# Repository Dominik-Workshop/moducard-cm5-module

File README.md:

# ModuCard CM5 module

## Overview

The **ModuCard CM5 Module** is a carrier board for the **Raspberry Pi Compute Module 5**.
It is designed to interface with the  [ModuCard backplane](https://github.com/KoNarRobotics/ModuCard-backplane), to create a more complex electronics system.

The module breaks out selected CM5 interfaces to front-panel connectors and it interfaces with the backplane.

### Key Features

- **Networking:** Gigabit Ethernet (RJ45)
- **Connectivity:** 2x USB 3.0 Type-A ports
- **Display:** 1x Full-size HDMI port
- **Storage:**
  - **Micro SD** card slot (for CM5 Lite variants)
  - **M.2 M-Key** slot (PCIe x1 Gen 3) for NVMe SSDs or AI accelerators.
- **System & Debug:**
  - **USB-C** port (front panel) for serial console access
  - **USB-C** port (vertical) for flashing the CM5 via `rpiboot`.
- **Backplane I/O:**
  - 2x **FD CAN** interfaces with on-board transceivers
  - 1x **USB 2.0**
- **Cooling:** 4-pin JST connector for the CM5 cooling fan.

<p align="center">
  
  <br>
  <em>Assembled ModuCard CM5 Module with Raspberry Pi Compute Module 5 and NVMe SSD.</em>
</p>

## Project Status

**Design:** ✅ → **Fabrication & Assembly:** ✅ → **Bring-up:** ✅

The project is **complete and ready for deployment**. All core features have been validated on physical hardware.

## Used Tools

- [KiCad](https://www.kicad.org/) - Schematic and PCB design

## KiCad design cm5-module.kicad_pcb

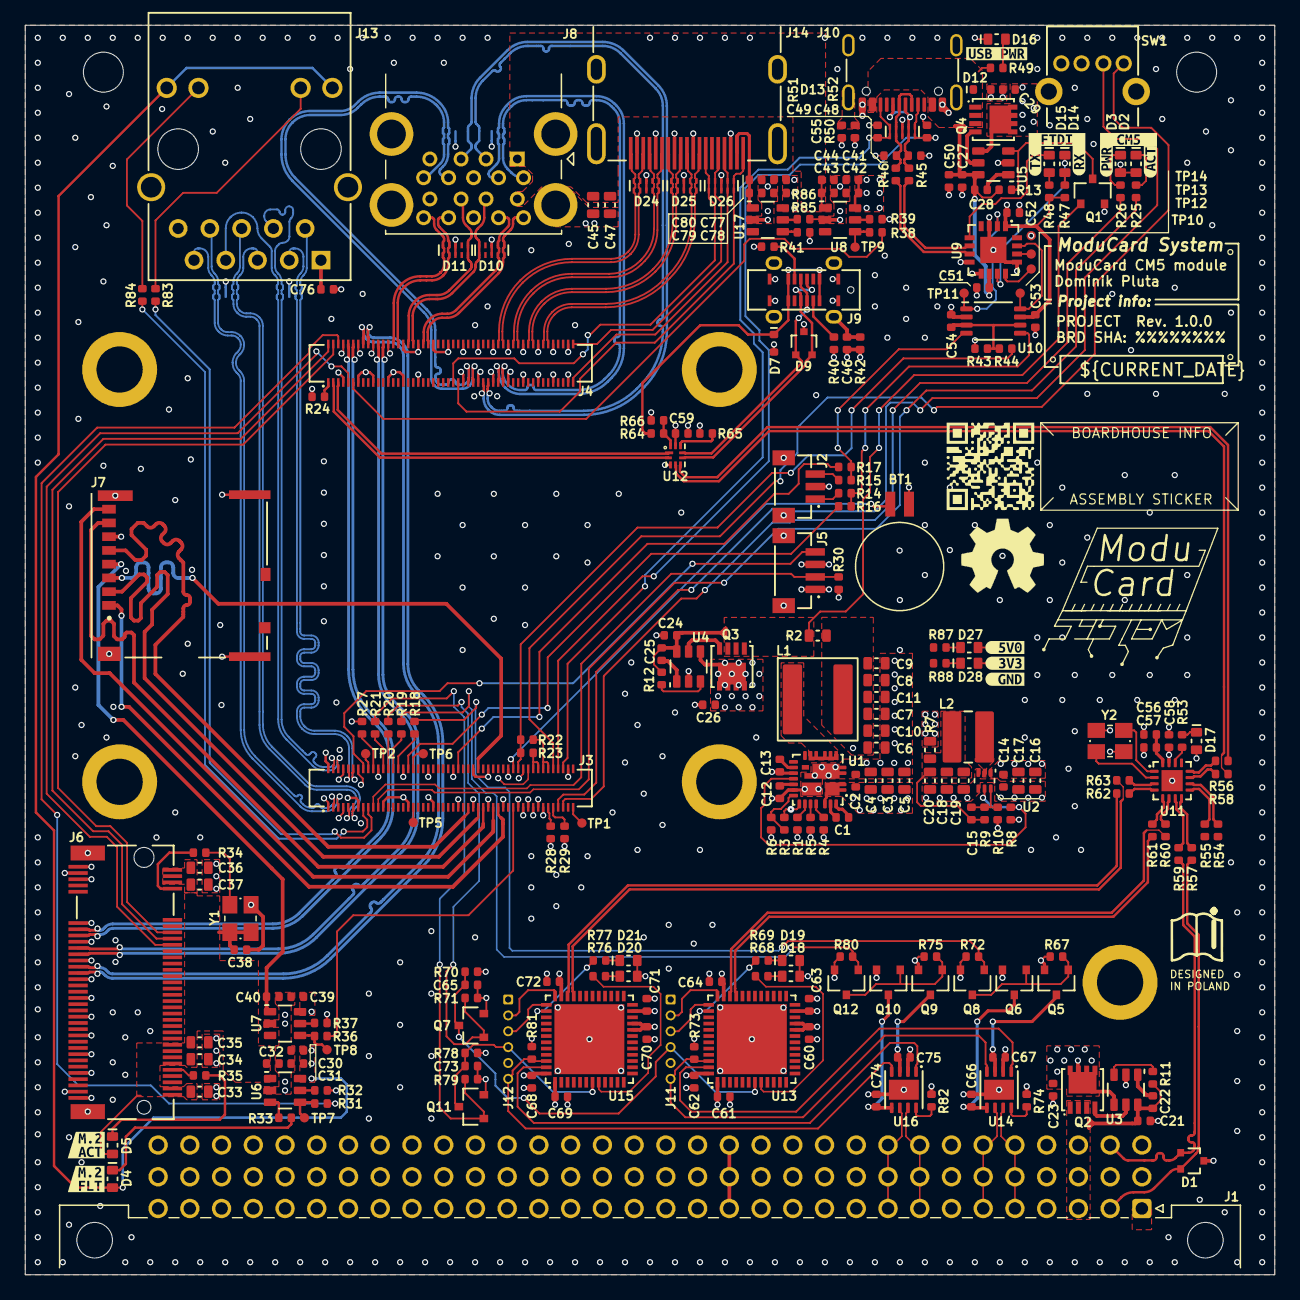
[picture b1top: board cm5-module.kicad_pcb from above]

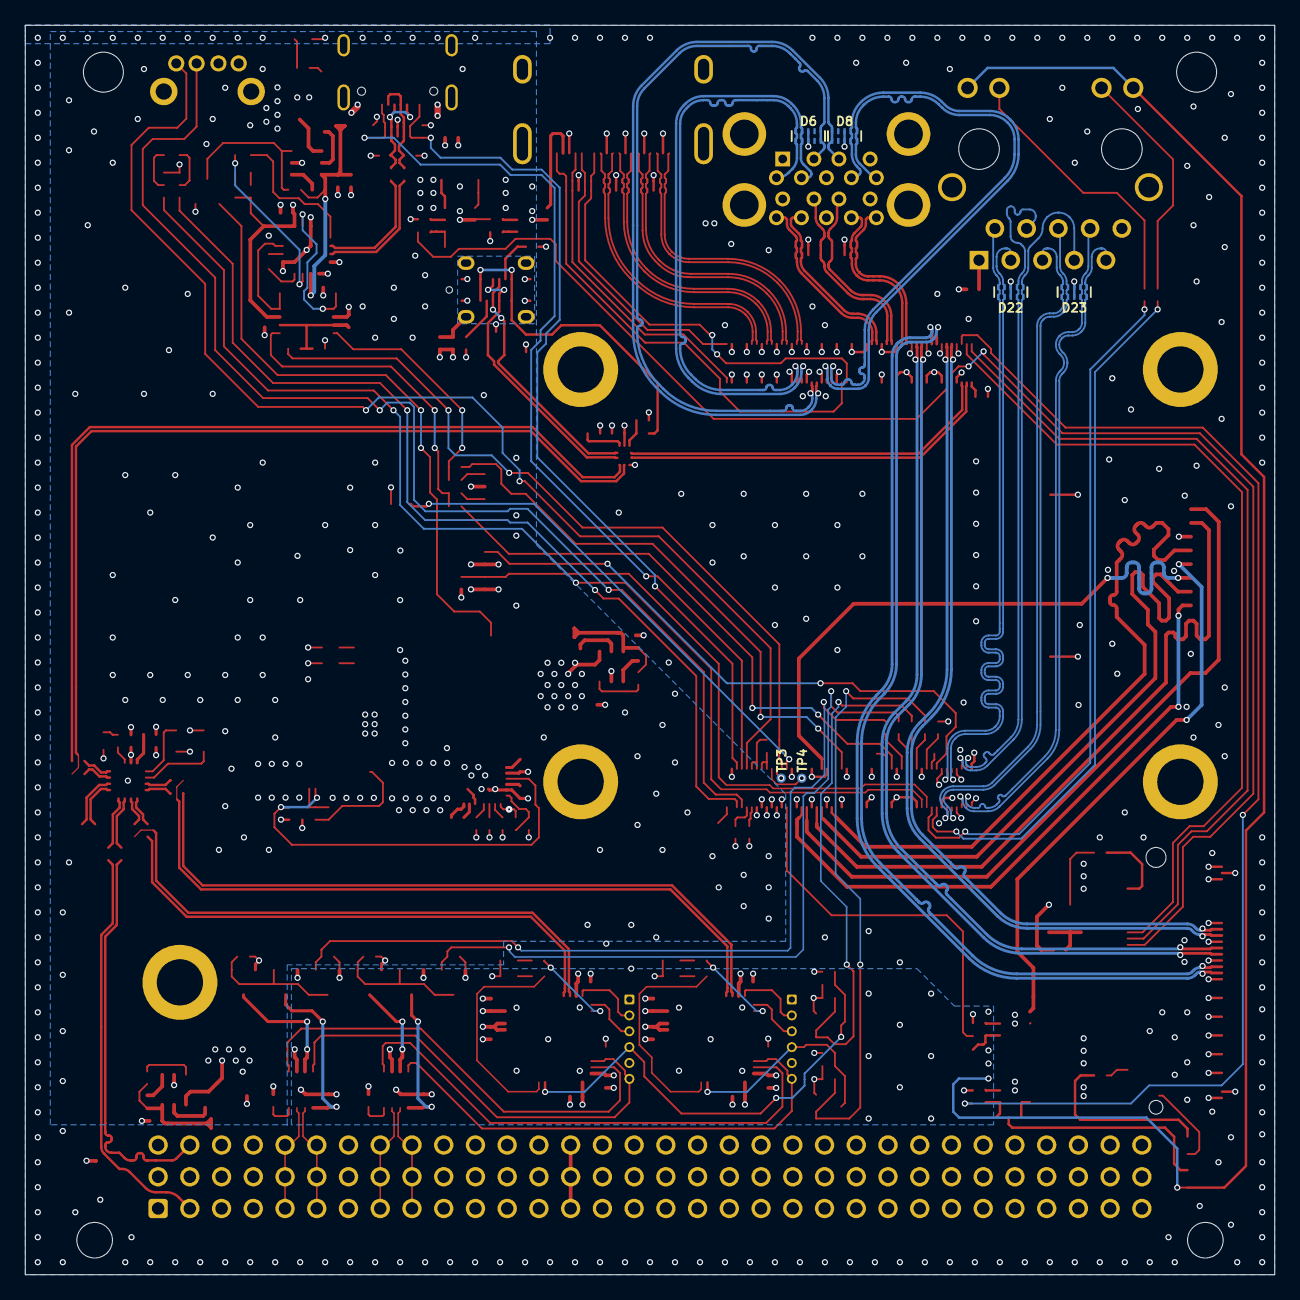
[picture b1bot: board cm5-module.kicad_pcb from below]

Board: 4 copper layers, 100.0 x 100.0 mm, 281 parts (6 on the bottom side), 223 nets.

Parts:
A1: RPi CM5; CM5
A2: M.2 M-key 2280; Card_M.2-2280-M-key
BT1: Battery_MS621FE-FL11E
C1, C2, C14, C21, C22, C23, C24, C25, C26, C27, C28, C29, C38, C46, C51, C52, C53, C54, C55, C57, C59, C60, C61, C62, C63, C64, C65, C66, C67, C68, C69, C70, C71, C72, C73, C74, C75, C76: C-100n-0402; C_0402_1005Metric
C3, C4, C5, C6, C7, C8, C9, C10, C11, C16, C17, C18, C19, C20, C33, C34, C35, C36, C37, C45, C47: C-10u-0603; C_0603_1608Metric
C12: C-1u-0402; C_0402_1005Metric
C13, C30, C31, C32, C39, C40, C41, C42, C43, C44, C50, C56, C58, C77, C78, C79, C80: C-4u7-0402; C_0402_1005Metric
C15, C48, C49: C-47p-0402; C_0402_1005Metric
D1, D9: TPD2E2U06DCKR; SOT-323
D2, D3, D4, D5, D14, D15, D16, D17, D18, D19, D20, D21, D27, D28: LED-R-0603_KT-0603R; LED_0603_1608Metric_R
D6, D8, D10, D11, D13, D22, D23, D24, D25, D26: PUSB3F96X; SOT1176-1
D7, D12: PESD5Z5; D_SOD-523
H1, H2, H3, H4: Spacer_M2.5_H3mm_9774030151R
H5: Spacer_M2.5_H2.5mm_9774025151R
J1: DIN-41612-connector_09031967921; Conn_DIN_41612_09031967921
J2: JST_SH_1x3_BM03B-SRSS-TB-LF-SN; Conn_JST_SH_1x3_BM03B-SRSS-TB
J3: CM5_1-100_3mm-stack; Conn_Socket_Hirose_DF40_2x50_DF40HC-3.0-100DS-0.4V
J4: CM5_101-200_3mm-stack; Conn_Socket_Hirose_DF40_2x50_DF40HC-3.0-100DS-0.4V
J5: JST_SH_1x4_BM04B-SRSS-TB-LF-SN; Conn_JST_SH_1x4_BM04B-SRSS-TB
J6: Bus_M.2_1-2199230-6; Bus_M.2_Socket_Key_M_TE_1-2199230-6
J7: MicroSD_5033981892
J8: USB-A_USB-303WSD-BRY; USB-A_Receptacle_USB-303WSD-BRY
J9: USB-C_TYPE-C_16PLT-H6.5; USB-C-Receptacle_TYPE-C_16PLT-H6.5
J10: USB-C_USB-310F-B-SU; USB-C-Receptacle_USB-310-B-SU
J11, J12: Programming connector; Custom-programming-connector-1x6_P1.27mm
J13: RJ45_HC612601A-M893-A
J14: HDMI-A_HDMI-19PIN-043; Conn_HDMI-A_HDMI-19PIN-043
L1: L-1u-20A-CJiang-FEXL0650A; L-CJiang-FEXL0650A
L2: L-1u5-6.5A-CJiang-FTC404030S; L-CJiang-FTC404030S
Q1, Q7, Q8, Q11, Q12: AO3400A; SOT-23-3
Q2, Q3, Q4: SIS472DN-T1-GE3; PowerPAK-1212-8_Single
Q5, Q6, Q9, Q10: AO3401A; SOT-23-3
R1, R6, R8, R10, R11, R12, R13, R30, R37, R64, R65, R66, R67, R70, R71, R72, R73, R74, R75, R78, R79, R80, R81, R82, R85, R86: R-10k-0402; R_0402_1005Metric
R2, R7: R-0R-22.4A-0603; R_0603_1608Metric
R3: R-73k2-0402; R_0402_1005Metric
R4, R5: R-499k-0402; R_0402_1005Metric
R9: R-45k3-0402; R_0402_1005Metric
R14, R15, R16, R17, R18, R19, R20, R21, R22, R23, R24, R27, R28, R29, R31, R34, R36, R38, R43, R44, R54, R55, R56, R57, R58, R59, R60, R61, R62, R63: R-0R-0402; R_0402_1005Metric
R25, R26, R33, R35, R47, R48, R49, R53, R68, R69, R76, R77, R83, R84, R87, R88: R-1k-0402; R_0402_1005Metric
R32, R39: R-2k2-0402; R_0402_1005Metric
R40, R41, R51, R52: R-5k1-0402; R_0402_1005Metric
R42, R50: R-330r-0402; R_0402_1005Metric
R45, R46: R-22R-0402; R_0402_1005Metric
SW1: SW_TL2243
TP1, TP2, TP3, TP4, TP5, TP6, TP7, TP8, TP9, TP10, TP11, TP12, TP13, TP14, TP15, TP16, TP17: TP_SMD_0.75mm
U1: SIC431AED-T1-GE3; MLP44-24L_4x4x0.75mm
U2: TPS564247DRLR; SOT-563
U3, U4, U5: LM74700QDBVRQ1; SOT-23-6
U6, U7, U8, U17: AP22615AWU-7; TSOT-23-6
U9: FT230XQ-R; QFN-16-1EP_4x4mm_P0.65mm_EP2.15x2.15mm
U10: NTS0102DP; TSSOP-8_3x3mm_P0.65mm
U11: CH334P; QFN-16-1EP_3x3mm_P0.5mm_EP1.75x1.75mm
U12: FSUSB42UMX; UFQFN-10_1.4x1.8mm_P0.4mm
U13, U15: STM32G431CBU6; UFQFPN-48-1EP_7x7mm_P0.5mm_EP5.7x5.7mm
U14, U16: TJA1044GTK_3Z; HVSON-8-1EP_3x3mm_P0.65mm_EP1.6x2.4mm
Y1: Oscillator_32.768kHz_OK2EL89CJI-111YLC-32.768K; Crystal_SMD_3225-4Pin_3.2x2.5mm
Y2: X322512MSB4SI; Crystal_SMD_3225-4Pin_3.2x2.5mm
kibuzzard-68E2CE3F: G***; kibuzzard-68E2CE3F
kibuzzard-68E2CE4E: G***; kibuzzard-68E2CE4E
kibuzzard-68E2CF9E: G***; kibuzzard-68E2CF9E
kibuzzard-68E2CF97: G***; kibuzzard-68E2CF97
kibuzzard-68E2CFD1: G***; kibuzzard-68E2CFD1
kibuzzard-68E2CFE8: G***; kibuzzard-68E2CFE8
kibuzzard-68E2D0C2: G***; kibuzzard-68E2D0C2
kibuzzard-68E2D09A: G***; kibuzzard-68E2D09A
kibuzzard-68E2D067: G***; kibuzzard-68E2D067
kibuzzard-68E507E1: G***; kibuzzard-68E507E1
kibuzzard-68E5088A: G***; kibuzzard-68E5088A
kibuzzard-68E50667: G***; kibuzzard-68E50667

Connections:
+3V3: C30.2, C31.2, C39.2, C59.2, C60.1, C61.1, C62.1, C63.1, C64.1, C68.1, C69.1, C70.1, C71.1, C72.1, D2.2 (A), D3.2 (A), D4.2 (A), D18.2 (A), D19.2 (A), D20.2 (A), D21.2 (A), D28.2 (A), J11.1, J12.1, J13.11, J13.14, Q6.2 (S), Q10.2 (S), R7.2, R30.2, R43.1, R70.2, R78.2, TP15.1, U6.6 (IN), U7.6 (IN), U12.9 (VCC), U13.1 (VBAT), U13.20 (VREF+), U13.21 (VDDA), U13.23 (VDD), U13.35 (VDD), U13.48 (VDD), U15.1 (VBAT), U15.20 (VREF+), U15.21 (VDDA), U15.23 (VDD), U15.35 (VDD), U15.48 (VDD)
+3V3_M2: C32.2, C33.2, C34.2, C35.2, C36.2, C37.2, C38.2, D5.2 (A), J6.2 (3V3), J6.4 (3V3), J6.12 (3V3), J6.14 (3V3), J6.16 (3V3), J6.18 (3V3), J6.70 (3V3), J6.72 (3V3), J6.74 (3V3), U6.1 (OUT), Y1.1 (EN), Y1.4 (VDD)
+5V: C14.1, C16.2, C17.2, C23.1, C26.1, C29.1, C41.2, C42.2, C58.2, C77.2, C78.2, D17.2 (A), D27.2 (A), J3.77 (+5V_(Input)), J3.79 (+5V_(Input)), J3.81 (+5V_(Input)), J3.83 (+5V_(Input)), J3.85 (+5V_(Input)), J3.87 (+5V_(Input)), J5.1, Q2.5 (D), Q3.5 (D), Q4.5 (D), Q5.2 (S), Q9.2 (S), R8.2, R67.2, R75.2, R85.1, TP16.1, U2.1 (V_{IN}), U3.4 (CATHODE), U4.4 (CATHODE), U5.4 (CATHODE), U8.6 (IN), U11.15 (5V), U17.6 (IN)
+5V_STDBY: C21.1, C22.1, J1.a3, J1.b3, J1.c3, Q2.1 (S), Q2.2 (S), Q2.3 (S), R11.2, U3.6 (ANODE)
+12V: C2.1, C3.2, C4.2, C5.2, J1.a11, J1.a12, J1.b11, J1.b12, J1.c11, J1.c12, R1.2, U1.1 (V_{IN}), U1.2 (V_{IN}), U1.22 (V_{IN}), U1.26 (V_{IN})
+24V: J1.a14, J1.b14, J1.c14
/Backplane/BACKPLANE.D+: D1.2, J1.a2, R57.2
/Backplane/BACKPLANE.D-: D1.1, J1.c2, R59.2
/Backplane/CAN_1.+: J1.a5, J1.b5, J1.c5, U14.7 (CANH)
/Backplane/CAN_1.-: J1.a6, J1.b6, J1.c6, U14.6 (CANL)
/Backplane/CAN_2.+: J1.a8, J1.b8, J1.c8, U16.7 (CANH)
/Backplane/CAN_2.-: J1.a9, J1.b9, J1.c9, U16.6 (CANL)
/CAN to USB 1/5V_TR: C67.1, Q5.3 (D), U14.3 (VCC)
/CAN to USB 1/EN_TRANSCEIVER: Q8.1 (G), R18.1, R72.2
/CAN to USB 1/RST_MCU: Q7.1 (G), R20.1, R71.2
/CAN to USB 1/RXD: J11.6, R73.2, U13.46 (PB8-BOOT0), U14.4 (RXD)
/CAN to USB 1/STAT_LED: R69.1, U13.38 (PA15)
/CAN to USB 1/SWCLK: J11.3, U13.37 (PA14)
/CAN to USB 1/SWDIO: J11.2, U13.36 (PA13)
/CAN to USB 1/TXD: U13.47 (PB9), U14.1 (TXD)
/CAN to USB 1/USB.D+: R60.2, U13.34 (PA12)
/CAN to USB 1/USB.D-: R61.2, U13.33 (PA11)
/CAN to USB 1/VIO_TR: C66.1, Q6.3 (D), U14.5 (VIO)
/CAN to USB 1/WORD_LED: R68.1, U13.8 (PA0)
/CAN to USB 1/~RST: C65.1, J11.4, Q7.3 (D), R70.1, U13.7 (PG10-~RST)
/CAN to USB 2/5V_TR: C75.1, Q9.3 (D), U16.3 (VCC)
/CAN to USB 2/EN_TRANSCEIVER: Q12.1 (G), R19.1, R80.2
/CAN to USB 2/RST_MCU: Q11.1 (G), R21.1, R79.2
/CAN to USB 2/RXD: J12.6, R81.2, U15.46 (PB8-BOOT0), U16.4 (RXD)
/CAN to USB 2/STAT_LED: R77.1, U15.38 (PA15)
/CAN to USB 2/SWCLK: J12.3, U15.37 (PA14)
/CAN to USB 2/SWDIO: J12.2, U15.36 (PA13)
/CAN to USB 2/TXD: U15.47 (PB9), U16.1 (TXD)
/CAN to USB 2/USB.D+: R62.2, U15.34 (PA12)
/CAN to USB 2/USB.D-: R63.2, U15.33 (PA11)
/CAN to USB 2/VIO_TR: C74.1, Q10.3 (D), U16.5 (VIO)
/CAN to USB 2/WORD_LED: R76.1, U15.8 (PA0)
/CAN to USB 2/~RST: C73.1, J12.4, Q11.3 (D), R78.1, U15.7 (PG10-~RST)
/CM5/+1V8_CM5: J3.88 (+1.8V_(Output)), J3.90 (+1.8V_(Output)), R22.1
/CM5/+3V3_CM5: J3.84 (+3.3V_(Output)), J3.86 (+3.3V_(Output)), R23.1
/CM5/CC1: D13.5 (CH4), D13.6 (CH4), J3.94 (CC1), J10.A5 (CC1), R52.2
/CM5/CC2: D13.1 (CH1), D13.10 (CH1), J3.96 (CC2), J10.B5 (CC2), R51.2
/CM5/CM5_RX: J2.1, R14.1
/CM5/CM5_TX: J2.3, R15.1
/CM5/CONSOLE.RX: R15.2, R17.2, U10.4 (A_{2})
/CM5/CONSOLE.TX: R14.2, R16.2, U10.5 (A_{1})
/CM5/ETH.D1+: D22.1 (CH1), D22.10 (CH1), J3.12 (Ethernet_Pair0_P), J13.2 (TD1+)
/CM5/ETH.D1-: D22.2 (CH2), D22.9 (CH2), J3.10 (Ethernet_Pair0_N), J13.3 (TD1-)
/CM5/ETH.D2+: D22.4 (CH3), D22.7 (CH3), J3.4 (Ethernet_Pair1_P), J13.4 (TD2+)
/CM5/ETH.D2-: D22.5 (CH4), D22.6 (CH4), J3.6 (Ethernet_Pair1_N), J13.7 (TD2-)
/CM5/ETH.D3+: D23.1 (CH1), D23.10 (CH1), J3.11 (Ethernet_Pair2_P), J13.5 (TD3+)
/CM5/ETH.D3-: D23.2 (CH2), D23.9 (CH2), J3.9 (Ethernet_Pair2_N), J13.6 (TD3-)
/CM5/ETH.D4+: D23.4 (CH3), D23.7 (CH3), J3.3 (Ethernet_Pair3_P), J13.8 (TD4+)
/CM5/ETH.D4-: D23.5 (CH4), D23.6 (CH4), J3.5 (Ethernet_Pair3_N), J13.9 (TD4-)
/CM5/FAN_PWM: J3.19 (FAN_PWM), J5.2, R30.1
/CM5/FAN_TACHO: J3.16 (FAN_TACHO), J5.4
/CM5/GPIO_VREF: J3.78 (GPIO_VREF), R22.2, R23.2, R44.1
/CM5/HDMI_0.CEC: D26.1 (CH1), D26.10 (CH1), J4.51 (HDMI0_CEC), J14.13 (CEC)
/CM5/HDMI_0.CLK+: D25.4 (CH3), D25.7 (CH3), J4.88 (HDMI0_CLK_P), J14.10 (CK+)
/CM5/HDMI_0.CLK-: D25.5 (CH4), D25.6 (CH4), J4.90 (HDMI0_CLK_N), J14.12 (CK-)
/CM5/HDMI_0.D0+: D25.1 (CH1), D25.10 (CH1), J4.82 (HDMI0_TX0_P), J14.7 (D0+)
/CM5/HDMI_0.D0-: D25.2 (CH2), D25.9 (CH2), J4.84 (HDMI0_TX0_N), J14.9 (D0-)
/CM5/HDMI_0.D1+: D24.4 (CH3), D24.7 (CH3), J4.76 (HDMI0_TX1_P), J14.4 (D1+)
/CM5/HDMI_0.D1-: D24.5 (CH4), D24.6 (CH4), J4.78 (HDMI0_TX1_N), J14.6 (D1-)
/CM5/HDMI_0.D2+: D24.1 (CH1), D24.10 (CH1), J4.70 (HDMI0_TX2_P), J14.1 (D2+)
/CM5/HDMI_0.D2-: D24.2 (CH2), D24.9 (CH2), J4.72 (HDMI0_TX2_N), J14.3 (D2-)
/CM5/HDMI_0.HOTPLUG: D26.5 (CH4), D26.6 (CH4), J4.53 (HDMI0_HOTPLUG), J14.19 (HPD)
/CM5/HDMI_0.SCL: D26.2 (CH2), D26.9 (CH2), J4.100 (HDMI0_SCL), J14.15 (SCL)
/CM5/HDMI_0.SDA: D26.4 (CH3), D26.7 (CH3), J4.99 (HDMI0_SDA), J14.16 (SDA)
/CM5/LED_ACT: J3.15 (Ethernet_nLED3), R84.2
/CM5/LED_LINK: J3.17 (Ethernet_nLED2), R83.2
/CM5/PCIe.REFCLK+: J4.10 (PCIe_CLK_P), J6.55 (REFCLK_P)
/CM5/PCIe.REFCLK-: J4.12 (PCIe_CLK_N), J6.53 (REFCLK_N)
/CM5/PCIe.RX0+: J4.16 (PCIe_RX_P), J6.43 (PER0_P)
/CM5/PCIe.RX0-: J4.18 (PCIe_RX_N), J6.41 (PER0_N)
/CM5/PCIe.TX0+: J4.22 (PCIe_TX_P), J6.49 (PET0_P)
/CM5/PCIe.TX0-: J4.24 (PCIe_TX_N), J6.47 (PET0_N)
/CM5/PCIe_PWR_EN: J4.6 (PCIE_PWR_EN), R31.1
/CM5/PMIC_EN: J3.99 (PMIC_ENABLE), TP1.1
/CM5/PWR_BTN: J3.92 (PWR_BUT), SW1.1 (BOTTOM_SW_1)
/CM5/SCL0: J3.80 (SCL0), TP3.1
/CM5/SCL1: J3.35 (ID_SC), TP5.1
/CM5/SDA0: J3.82 (SDA0), TP4.1
/CM5/SDA1: J3.36 (ID_SD), TP6.1
/CM5/SD_CARD.CLK: J3.57 (SD_CLK), J7.5 (CLK)
/CM5/SD_CARD.CMD: J3.62 (SD_CMD), J7.3 (CMD)
/CM5/SD_CARD.DAT0: J3.63 (SD_DAT0), J7.7 (DAT0)
/CM5/SD_CARD.DAT1: J3.67 (SD_DAT1), J7.8 (DAT1)
/CM5/SD_CARD.DAT2: J3.69 (SD_DAT2), J7.1 (DAT2)
/CM5/SD_CARD.DAT3: J3.61 (SD_DAT3), J7.2 (DAT3/CD)
/CM5/SD_PWR_ON: J3.75 (SD_PWR_ON), R36.1
/CM5/UART2_RX: J3.34 (GPIO5), R16.1
/CM5/UART2_TX: J3.54 (GPIO4), R17.1
/CM5/USB.D+: J4.5 (USB2_P), U12.1 (D+)
/CM5/USB.D-: J4.3 (USB2_N), U12.2 (D-)
/CM5/USB_SS_0.D+: D11.1 (CH1), D11.10 (CH1), J4.34 (USB3-0-D_P), J8.12 (D+)
/CM5/USB_SS_0.D-: D10.5 (CH4), D10.6 (CH4), J4.36 (USB3-0-D_N), J8.11 (D-)
/CM5/USB_SS_0.RX+: D11.4 (CH3), D11.7 (CH3), J4.30 (USB3-0-RX_P), J8.15 (SSRX+)
/CM5/USB_SS_0.RX-: D11.5 (CH4), D11.6 (CH4), J4.28 (USB3-0-RX_N), J8.14 (SSRX-)
/CM5/USB_SS_0.TX+: D10.1 (CH1), D10.10 (CH1), J4.42 (USB3-0-TX_P), J8.18 (SSTX+)
/CM5/USB_SS_0.TX-: D10.2 (CH2), D10.9 (CH2), J4.40 (USB3-0-TX_N), J8.17 (SSTX-)
/CM5/USB_SS_1.D+: D8.1 (CH1), D8.10 (CH1), J4.63 (USB3-1-D_P), J8.3 (D+)
/CM5/USB_SS_1.D-: D6.5 (CH4), D6.6 (CH4), J4.65 (USB3-1-D_N), J8.2 (D-)
/CM5/USB_SS_1.RX+: D8.4 (CH3), D8.7 (CH3), J4.59 (USB3-1-RX_P), J8.6 (SSRX+)
/CM5/USB_SS_1.RX-: D8.5 (CH4), D8.6 (CH4), J4.57 (USB3-1-RX_N), J8.5 (SSRX-)
/CM5/USB_SS_1.TX+: D6.1 (CH1), D6.10 (CH1), J4.71 (USB3-1-TX_P), J8.9 (SSTX+)
/CM5/USB_SS_1.TX-: D6.2 (CH2), D6.9 (CH2), J4.69 (USB3-1-TX_N), J8.8 (SSTX-)
/CM5/VBAT: BT1.1 (+), J3.76 (VBAT)
/CM5/VBUS_EN: J4.11 (VBUS_EN), R38.1
/CM5/~BT_DIS: J3.91 (BT_nDisable), R29.2
/CM5/~EEPROM_WP: J3.20 (EEPROM_nWP), R27.2
/CM5/~LED_ACT: J3.21 (LED_nACT), R25.1
/CM5/~LED_PWR: J3.95 (LED_nPWR), R26.1
/CM5/~PCIe_CLKREQ: J4.2 (PCIe_nCLKREQ), J6.52 (~CLKREQ)
/CM5/~PCIe_PERST: J4.9 (PCIe_nRST), J6.50 (~PERST)
/CM5/~PCIe_WAKE: J4.4 (PCIE_nWAKE), J6.54 (~PEWAKE)
/CM5/~RPIBOOT: J3.93 (nRPIBOOT), SW1.2 (BOTTOM_SW_1)
/CM5/~WiFi_DIS: J3.89 (WiFi_nDisable), R28.2
/HDMI/EN: R85.2, U17.4 (EN)
/HDMI/HDMI_+5V: C79.2, C80.2, J14.18 (+5V), U17.1 (OUT)
/HDMI/ISET: R86.1, U17.5 (ISET)
/M.2/EN: R31.2, TP7.1, U6.4 (EN)
/M.2/ISET: R32.1, U6.5 (ISET)
/M.2/LED: J6.10 (LED), R35.1
/M.2/SUSCLK: R34.2, Y1.3 (OUT)
/M.2/SUSCLK_R: J6.68 (SUSCLK), R34.1
/M.2/~FLG: R33.1, U6.3 (~FLG)
/Power/3V3_DC-DC: C15.2, C18.2, C19.2, C20.2, L2.2, R7.1, R9.2
/Power/3V3_EN: R8.1, U1.14 (P_{GOOD}), U2.5 (EN)
/Power/3V3_FB: C15.1, R9.1, R10.2, U2.6 (FB)
/Power/3V3_SW: L2.1, U2.2 (SW)
/Power/5V: C24.1, C25.1, Q1.1 (G), Q3.1 (S), Q3.2 (S), Q3.3 (S), R2.2, R12.2, U4.6 (ANODE)
/Power/5V_BOOT: C1.2, U1.23 (BOOT)
/Power/5V_DC-DC: C6.2, C7.2, C8.2, C9.2, C10.2, C11.2, L1.2, R2.1, R3.1, U1.18 (V_{OUT})
/Power/5V_EN: R1.1, U1.19 (EN)
/Power/5V_FB: R3.2, R6.2, U1.17 (FB)
/Power/5V_MODE1: R4.2, U1.21 (MODE1)
/Power/5V_MODE2: R5.2, U1.20 (MODE2)
/Power/5V_PHASE: C1.1, U1.24 (PHASE)
/Power/5V_SW: L1.1, U1.5 (SW), U1.6 (SW), U1.7 (SW), U1.8 (SW), U1.9 (SW)
/Power/5V_USB_IN: C27.1, C28.1, C50.2, C51.2, D12.1 (C), J10.A4 (VBUS), J10.A9 (VBUS), J10.B4 (VBUS), J10.B9 (VBUS), Q4.1 (S), Q4.2 (S), Q4.3 (S), R13.2, R49.2, U5.6 (ANODE), U9.10 (V_{CC})
/Power/5V_VDD: C12.2, U1.15 (V_{DD})
/Power/5V_VDRV: C13.2, U1.12 (V_{DRV})
/Power/Ideal diode 0/~DISABLE: R11.1, U3.3 (EN)
/Power/Ideal diode 1/~DISABLE: R12.1, U4.3 (EN)
/Power/Ideal diode 2/~DISABLE: Q1.3 (D), R13.1, U5.3 (EN)
/SD card/EN: R36.2, TP8.1, U7.4 (EN)
/SD card/ISET: R37.1, U7.5 (ISET)
/SD card/SD_+3V3: C40.2, J7.4 (VDD), U7.1 (OUT)
/USB console/D+: R45.2, U9.6 (D+)
/USB console/D-: R46.2, U9.7 (D-)
/USB console/FTDI_CBUS0: TP12.1, U9.12 (CBUS0)
/USB console/FTDI_CBUS3: TP13.1, U9.14 (CBUS3)
/USB console/FTDI_LED_RX: D14.1 (C), U9.11 (CBUS1)
/USB console/FTDI_LED_TX: D15.1 (C), U9.5 (CBUS2)
/USB console/FTDI_VCCIO: C52.2, C53.2, R47.2, R48.2, U9.1 (V_{CCIO}), U9.8 (3V3_{OUT}), U9.9 (~RESET), U10.7 (VCC_{B})
/USB console/USB_D+: C48.2, D13.4 (CH3), D13.7 (CH3), J10.A6 (D+), J10.B6 (D+), R45.1
/USB console/USB_D-: C49.2, D13.2 (CH2), D13.9 (CH2), J10.A7 (D-), J10.B7 (D-), R46.1
/USB hub/USB_1_R.D+: R54.1, U11.10 (DP1)
/USB hub/USB_1_R.D-: R55.1, U11.9 (DM1)
/USB hub/USB_2_R.D+: R57.1, U11.8 (DP2)
/USB hub/USB_2_R.D-: R59.1, U11.7 (DM2)
/USB hub/USB_3_R.D+: R60.1, U11.6 (DP3)
/USB hub/USB_3_R.D-: R61.1, U11.5 (DM3)
/USB hub/USB_4_R.D+: R62.1, U11.4 (DP4)
/USB hub/USB_4_R.D-: R63.1, U11.3 (DM4)
/USB hub/USB_HUB.D+: R56.1, U12.5 (HSD1+)
/USB hub/USB_HUB.D-: R58.1, U12.4 (HSD1-)
/USB hub/USB_HUB_R.D+: R56.2, U11.12 (DPU)
/USB hub/USB_HUB_R.D-: R58.2, U11.11 (DMU)
/USB hub/XI: U11.2 (XI), Y2.3
/USB hub/XO: U11.1 (XO), Y2.1
/USB switch/SEL: D7.1 (C), J9.A4 (VBUS), J9.A9 (VBUS), J9.B4 (VBUS), J9.B9 (VBUS), R64.2
/USB switch/USB_2.D+: D9.1, J9.A6 (D+), J9.B6 (D+), U12.7 (HSD2+)
/USB switch/USB_2.D-: D9.2, J9.A7 (D-), J9.B7 (D-), U12.6 (HSD2-)
/USB/+VBUS: C43.2, C44.2, C45.2, C47.2, J8.1 (VBUS), J8.10 (VBUS), U8.1 (OUT)
/USB/EN: R38.2, TP9.1, U8.4 (EN)
/USB/ISET: R39.1, U8.5 (ISET)
GND: BT1.2 (-), C2.2, C3.1, C4.1, C5.1, C6.1, C7.1, C8.1, C9.1, C10.1, C11.1, C12.1, C13.1, C14.2, C16.1, C17.1, C18.1, C19.1, C20.1, C21.2, C23.2, C24.2, C26.2, C27.2, C29.2, C30.1, C31.1, C32.1, C33.1, C34.1, C35.1, C36.1, C37.1, C38.1, C39.1, C40.1, C41.1, C42.1, C43.1, C44.1, C45.1, C46.1, C47.1, C48.1, C49.1, C50.1, C51.1, C52.1, C53.1, C54.1, C55.1, C56.1, C57.1, C58.1, C59.1, C60.2, C61.2, C62.2, C63.2, C64.2, C65.2, C66.2, C67.2, C68.2, C69.2, C70.2, C71.2, C72.2, C73.2, C74.2, C75.2, C76.1, C77.1, C78.1, C79.1, C80.1, D1.3, D6.3 (GND), D6.8 (GND), D7.2 (A), D8.3 (GND), D8.8 (GND), D9.3, D10.3 (GND), D10.8 (GND), D11.3 (GND), D11.8 (GND), D12.2 (A), D13.3 (GND), D13.8 (GND), D16.1 (C), D22.3 (GND), D22.8 (GND), D23.3 (GND), D23.8 (GND), D24.3 (GND), D24.8 (GND), D25.3 (GND), D25.8 (GND), D26.3 (GND), D26.8 (GND), H1.1, H2.1, H3.1, H4.1, H5.1, J1.a1, J1.a4, J1.a7, J1.a10, J1.a13, J1.a15, J1.a32, J1.b1, J1.b2, J1.b4, J1.b7, J1.b10, J1.b13, J1.b15, J1.b32, J1.c1, J1.c4, J1.c7, J1.c10, J1.c13, J1.c15, J1.c32, J2.2, J2.MP, J3.1 (GND), J3.2 (GND), J3.7 (GND), J3.8 (GND), J3.13 (GND), J3.14 (GND), J3.22 (GND), J3.23 (GND), J3.32 (GND), J3.33 (GND), J3.42 (GND), J3.43 (GND), J3.52 (GND), J3.53 (GND), J3.59 (GND), J3.60 (GND), J3.65 (GND), J3.66 (GND), J3.71 (GND), J3.74 (GND), J3.98 (GND), J4.7 (GND), J4.8 (GND), J4.13 (GND), J4.14 (GND), J4.19 (GND), J4.20 (GND), J4.25 (GND), J4.26 (GND), J4.31 (GND), J4.32 (GND), J4.37 (GND), J4.38 (GND), J4.44 (GND), J4.50 (GND), J4.55 (GND), J4.56 (GND), J4.61 (GND), J4.62 (GND), J4.67 (GND), J4.68 (GND), J4.73 (GND), J4.74 (GND), J4.79 (GND), J4.80 (GND), J4.85 (GND), J4.86 (GND), J4.91 (GND), J4.92 (GND), J4.97 (GND), J4.98 (GND), J5.3, J5.MP, J6.1 (GND), J6.3 (GND), J6.9 (GND), J6.15 (GND), J6.21 (GND), J6.27 (GND), J6.33 (GND), J6.39 (GND), J6.45 (GND), J6.51 (GND), J6.57 (GND), J6.71 (GND), J6.73 (GND), J6.75 (GND), J6.MP1 (MP), J6.MP2 (MP), J7.6 (VSS), J7.11 (SHIELD), J8.4 (GND), J8.7 (DRAIN), J8.13 (GND), J8.16 (DRAIN), J8.19 (SHIELD), J9.A1 (GND), J9.A12 (GND), J9.B1 (GND), J9.B12 (GND), J10.A1 (GND), J10.A12 (GND), J10.B1 (GND), J10.B12 (GND), J11.5, J12.5, J13.10 (GND), J13.SH, J14.2 (D2S), J14.5 (D1S), J14.8 (D0S), J14.11 (CKS), J14.17 (GND), J14.SH, Q1.2 (S), Q7.2 (S), Q8.2 (S), Q11.2 (S), Q12.2 (S), R4.1, R5.1, R6.1, R10.1, R24.2, R27.1, R28.1, R29.1, R32.2, R37.2, R39.2, R40.1, R41.1, R42.1, R50.1, R51.1, R52.1, R65.1, R66.1, R71.1, R72.1, R73.1, R74.1, R79.1, R80.1, R81.1, R82.1, R86.2, R87.1, R88.1, SW1.3 (BOTTOM_SW_2), SW1.4 (BOTTOM_SW_2), SW1.5 (SH), SW1.6 (SH), TP14.1, TP17.1, U1.3 (P_{GND}), U1.4 (P_{GND}), U1.13 (P_{GND}), U1.16 (A_{GND}), U1.25 (A_{GND}), U1.27 (P_{GND}), U2.3 (GND), U2.4 (AGND), U3.2 (GND), U4.2 (GND), U5.2 (GND), U6.2 (GND), U7.2 (GND), U8.2 (GND), U9.3 (GND), U9.13 (GND), U9.17 (GND), U10.2 (GND), U11.17 (GND), U12.3 (GND), U13.49 (VSS), U14.2 (GND), U14.9 (GND), U15.49 (VSS), U16.2 (GND), U16.9 (GND), U17.2 (GND), Y1.2 (GND), Y2.2 (SH), Y2.4 (SH)
unnamed: D2.1 (C), R25.2
unnamed: D3.1 (C), R26.2
unnamed: D4.1 (C), R33.2
unnamed: D5.1 (C), R35.2
unnamed: D14.2 (A), R47.1
unnamed: D15.2 (A), R48.1
unnamed: D16.2 (A), R49.1
unnamed: D17.1 (C), R53.2
unnamed: D18.1 (C), R68.2
unnamed: D19.1 (C), R69.2
unnamed: D20.1 (C), R76.2
unnamed: D21.1 (C), R77.2
unnamed: D27.1 (C), R87.2
unnamed: D28.1 (C), R88.2
unnamed: J3.18 (Ethernet_SYNC_OUT), TP2.1
unnamed: J3.30 (GPIO6), R18.2
unnamed: J3.28 (GPIO13), R19.2
unnamed: J3.26 (GPIO19), R20.2
unnamed: J3.24 (GPIO26), R21.2
unnamed: J4.1 (USB_OTG_ID), R24.1
unnamed: J9.A5 (CC1), R40.2
unnamed: J9.B5 (CC2), R41.2
unnamed: C46.2, J9.S1 (SHIELD), R42.2
unnamed: C55.2, J10.S1 (SHIELD), R50.2
unnamed: C76.2, J13.1 (CT)
unnamed: J13.12, R83.1
unnamed: J13.13, R84.1
unnamed: Q2.4 (G), U3.5 (GATE)
unnamed: Q3.4 (G), U4.5 (GATE)
unnamed: Q4.4 (G), U5.5 (GATE)
unnamed: Q5.1 (G), Q6.1 (G), Q8.3 (D), R67.1
unnamed: Q9.1 (G), Q10.1 (G), Q12.3 (D), R75.1
unnamed: C22.2, U3.1 (VCAP)
unnamed: C25.2, U4.1 (VCAP)
unnamed: C28.2, U5.1 (VCAP)
unnamed: TP10.1, U9.15 (TXD), U10.8 (B_{1})
unnamed: TP11.1, U9.2 (RXD), U10.1 (B_{2})
unnamed: C54.2, R43.2, R44.2, U10.3 (VCC_{A}), U10.6 (OE)
unnamed: C56.2, C57.2, U11.16 (3V3)
unnamed: R53.1, U11.14 (PGANG)
unnamed: R64.1, R66.2, U12.10 (SEL)
unnamed: R65.2, U12.8 (~OE)
unnamed: R74.2, U14.8 (STB)
unnamed: R82.2, U16.8 (STB)

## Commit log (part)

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2025-07-05 [#1] Init project
2025-07-16 [#1] WIP: Change components to ones from the global library, refactor schematic
2025-08-01 [#1] Change components to ones from the global library, add debug console, refactor schematic
2025-08-01 [#1] Add bus colors, rename PCIe signals
2025-08-01 [#1] Add debug UART connector
2025-08-08 [#1] Add level shifter for UART debug, update footprints from library
2025-08-19 [#1] Re-annotate schematic
2025-08-22 [#1] Sync PCB with schematic, draft component placement
2025-08-22 [#1] Add power section
2025-08-30 [#1] WIP: Refactor schematic
2025-09-11 [#1] Finish schematic design of the 3V3 DC-DC converter
2025-09-11 [#1] Update CM5 connectors symbols, connect its misc pins
2025-09-12 [#1] Add cooling fan connector
2025-09-12 Add mock-up render
2025-09-13 [#1] Add USB to CAN schematic, add power flags to 5V and 3V3
2025-09-13 [#1] Rename USB schematic sheet
2025-09-14 [#1] Add USB switch and 0R to USB hub data lines, minor schematic refactor
2025-09-15 [#3] Align PCB to grid, start placement of key components
    Position the M.2 connector, try positioning of front panel connectors
2025-09-16 [#3] Set differential pair parameters for all interfaces
2025-09-20 [#3] Fix 3V3 DC-DC converter schematic, change one USB-C to a vertical one, start layout
2025-09-20 [#3] Adjust front panel mounting holes positioning and rails keepout area
2025-09-20 [#3] Position front panel connectors
2025-09-20 [#3] Add TVS, route HDMI and fanout ETH
2025-09-21 [#3] Layout HDMI, PCIe and ETH differential pairs
2025-09-21 [#3] Layout USB power
2025-09-27 [#3] Continue layout, minor schematic fixes, add power switch for CAN transceiver 5V rail
2025-09-27 [#3] WIP: Clear ERC, re-annotate schematic
2025-09-27 [#3] Layout DC-DC converters
2025-09-27 [#3] Add 0R to DC-DC outputs, add 5V->3V3 power sequencing
2025-09-27 [#3] Add CM5 RTC battery
2025-09-27 [#3] WIP: Layout power and USB console
2025-09-28 [#3] Start USB layout
2025-09-28 [#3] Move the 5V DC-DC ideal diode, position fan and debug JST connectors
2025-09-28 [#3] Layout SD card connector
    NOTE: Used 0.3mm traces instead of 0.35mm ones on SDIO lines due to
    limited space
2025-09-29 [#3] Layout M.2 power
2025-10-04 [#3] Layout USB
2025-10-05 [#3] Layout USB to CAN converter and remaining low speed signals
2025-10-05 [#3] Change schematic sheets order
2025-10-05 [#3] Re-annotate schematic
2025-10-05 [#3] Position components designators on PCB
2025-10-05 [#3] Clear ERC
2025-10-05 [#3] Improve LEDs descriptions on the PCB
2025-10-05 [#3] Add via stitching
2025-10-06 [#3] Add GND pours on top and bottom
2025-10-07 [#3] Add 5V and 3V3 power indicator LEDs and test-points
2025-10-07 [#3] Add description of USB to CAN LEDs
2025-10-07 [#3] Clear DRC
2025-10-08 [#5] Add programming connector pinout on silkscreen, cleanup GND pours
2025-10-08 [#5] Round and length match USB 2.0 differential pairs
2025-10-08 [#5] Move the KiCad project to pcb folder
2025-10-08 [#5] Assign GND net class
2025-10-08 [#5] Refactor the schematic
2025-10-09 [#5] Disable 5V_STDBY when main 5V rail is present
2025-10-09 [#5] Add decoupling capacitor closer to the SD card, update programming connector from library
2025-10-09 [#5] Add more 3V3 zone connecting vias, convert text in logos to polygons
2025-10-09 [#5] Add more 3V3 zone connecting vias, convert text in logos to polygons, update date
2025-10-10 Update PCB render
2025-10-10 Add JST debug and fan connectors descriptions on silkscreen
2025-10-10 Use NPTH for 3.2mm holes instead of edge cuts circle
2025-10-12 Add PCB blender model
2025-10-12 TMP: Add markings images
2025-10-13 Add models with markings on PCB blend
2025-11-17 Update Used Tools section in README
2025-11-23 Update project status in README
